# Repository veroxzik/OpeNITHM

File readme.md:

# OpeNITHM

This repository contails files related to OpeNITHM.

Firmware, schematics, board layout, and CAD files are included in this repo. Please see the CAD directory for the original 3d printed version, or the v2-cad directory for the laser cut version. 

## List of Electronics

OpeNITHM is designed for the Teensy LC.

#### Why use Teensy and not Arduino?

The biggest reason is that Teensy has built in capacitive sensing, which is how OpeNITHM fuctions. You have to fake it on Arduino using very controlled analog reads, and it is nowhere near as sensitive. In my (VXZK's) experience, it was simply impossible to use an Arduino to do the capacitive sensing required for this project.

I chose the Teensy LC as it is the lowest cost Teensy model available with capacitive sensing. The firmware and PCB are designed for this board alone; significant modifications may be required for any other version.

There is an alternative build using an Arduino Pro Micro and 2 MPR121s as a branch in this repo, but it is not maintained and not recommended. You're on your own with that one!

### Teensy LC Build

Links are mostly suggestions (except the Teensy, which is only officially available through the PJRC site and authorized resellers).  
(VXZK: I've heard a lot of trouble regarding good quality IR leds and phototransistors, so I've included specific links to the ones I purchased and has worked well for me.)  

The links below also assume you want to socket your Teensy and multiplexers for later use. You can solder them directly, if you'd like.  
If you are going to solder your sensors directly to the PCB, it is not necessary buy the 0.1" Pin Header, Right Angle. Otherwise, include female 0.1" sockets for your sensors (commonly referred to as Dupont connectors).  

| Part | Link | Qty |
| --- | --- |:---:|
| Teensy LC | https://www.pjrc.com/store/teensylc.html | 1 |
| Teensy LC Breakout Board | this Github, Circuit-Teensy32 folder contains gerbers | 1 |
| 74HC4051 Multiplexer Breakout Board | [Aliexpress][1] | 4 |
| 0.1" Pin Header, 1 row, 40 pos | [Aliexpress (qty 10)][2] | 2 |
| 0.1" Pin Header, Right Angle, 2 row, 24 pos | [LCSC][3] | 2 |
| 0.1" Socket, Straight, 1 row, 14 pos | [LCSC][4] | 2 |
| 0.1" Socket, Straight, 1 row, 5 pos | [LCSC][5] | 2 |
| 0.1" Socket, Straight, 1 row, 11 pos | [LCSC][6] | 2 |
| 0.1" Socket, Straight, 1 row, 8 pos | [LCSC][7] | 2 |
| 51k ohm Resistor, 1/6W or 1/8W | LCSC or Aliexpress | 6 |
| 33 ohm Resistor, 1/4W, 1/6W, or 1/8W | LCSC or Aliexpress | 3 |
| 1m WS2812B RGB 5V LED Strip, 30LED Per Meter | [Aliexpress][8] | 1 |
| IR LED and Phototransistor | [Ebay (Qty 20 pairs)][9] | 6 |

[1]: https://www.aliexpress.com/item/32807771098.html
[2]: https://www.aliexpress.com/item/665534073.html
[3]: https://lcsc.com/product-detail/New-Arrivals_XFCN-PZ254R-12-24P_C492440.html
[4]: https://lcsc.com/product-detail/Pin-Header-Female-Header_Boom-Precision-Elec-Female-header-2-54-1-14P_C52711.html
[5]: https://lcsc.com/product-detail/Pin-Header-Female-Header_Boom-Precision-Elec-2-54mm-1-5p-Female-header_C50950.html
[6]: https://lcsc.com/product-detail/Pin-Header-Female-Header_Changjiang-Connectors-A2541HWV-11P_C225508.html
[7]: https://lcsc.com/product-detail/Pin-Header-Female-Header_Boom-Precision-Elec-2-54mm-1-8P-Straight-Female-header_C27438.html
[8]: https://www.aliexpress.com/item/2036819167.html
[9]: https://www.ebay.com/itm/40pcs-5mm-Infrared-LED-940nm-Emitter-Diode-and-IR-Receiver-Set/252235145540

## Board Revision and Sensors

As of 2020-07-17, the recommended board version is v2.1, which features inputs for 32 sensors. This best replicates the feeling of the arcade. Previous versions used 16 sensors. If you still wish to make a 16 key version, you can order the v2.1 but only populate two of the multiplexers. This is not really recommended.

### Older versions

For v2.0 and v1.1, bridge pins 17 and 24 for best throughput of RGB lighting and select the appropriate setting in `Config.h`.

## Installing on Teensy LC

**NOTE:** This firmware is *only* written to work for the Teensy LC. Do *not* use Teensy 2.0, Teensy 3.x, or Teensy 4.x

Locate your `arduino` folder (usually `C:\Program Files (x86)\arduino`).

#### I have a fresh install of Teensyduino, or have never modified my USB profiles

Copy `Firmware/Teensy/boards.txt` to `arduino\hardware\teensy\avr\` and overwrite the existing.

Copy `Firmware/Teensy/teensy3` to `arduino\hardware\teensy\avr\cores\teensy3` and overwrite any conflicts.

Copy `Firmware/FastLED/WS2812Serial.cpp` and `Firmware/FastLED/WS2812Serial.h` to `arduino\hardware\teensy\avr\libraries\WS2812Serial` and overwrite the existing.

Copy `Firmware/FastLED/FastLED.cpp` and `Firmware/FastLED/FastLED.h` to `[My Documents]\Arduino\libraries\FastLED\` and overwrite the existing.

#### I am applying the changes manually

See [the firmware readme](Firmware/README.md) for more information.

## Configuring the Firmware and IDE

There are a number of options built into the firmware to give you flexibility in your implementation. These are presented as preprocessor defines that can be commented and uncommented to fit.

All user-editable defines are in `Config.h`, see the comments for additional information.

`PinConfig.h` contains the defintions of each pin. This does not need to be edited if using the gerbers from this repo.

If you do not have the FastLED library installed, do so though the `Tools->Manage Libraries` menu. You will also need the WS2812Serial library, which should be installed when you install Teensyduino.

#### Compiling

Select `Teensy LC` from `Tools->Board`, then select `Serial + NKRO Keyboard`.

Prior to compilation, review the (numerous) options available to the end user in `Config.h`. Comment and uncomment the corresponding options that match your setup.

## Running the Software

#### Configuring

To be revised.

#### Power On

To be revised.

#### Output

By default, the program will run in NKRO Keyboard mode. The specific keyboard keys are set in `USBOutput.cpp`, but are listed here in order of left to right:
```
a z s x d c f v g b h n j m k ,
```
When a second finger touches the pad, the following keys are pressed in order of left to right
```
1 q 2 w 3 e 4 r 5 t 6 y 7 u 8 i
```

By default, the air sensor functions as follows:
- `Home` is held as long as any sensor is triggered and released when there are no sensors triggered.
- `End` is pressed when any motion is detected, as long as the hand was previously in front of the sensors.
- `Page Up` is pressed and released when the sensor detections movement upwards.
- `Page Down` is pressed and released when the sensor detections movement downwards.

If `#define IR_SENSOR_KEY` is uncommented, each air sensor will report back individually. The default binding from bottom to top is:
```
/ . ' ; ] [
```
Per US QWERTY layout.

## Credits

Thanks to SpaghettiSnail for the LED Support Peg model!

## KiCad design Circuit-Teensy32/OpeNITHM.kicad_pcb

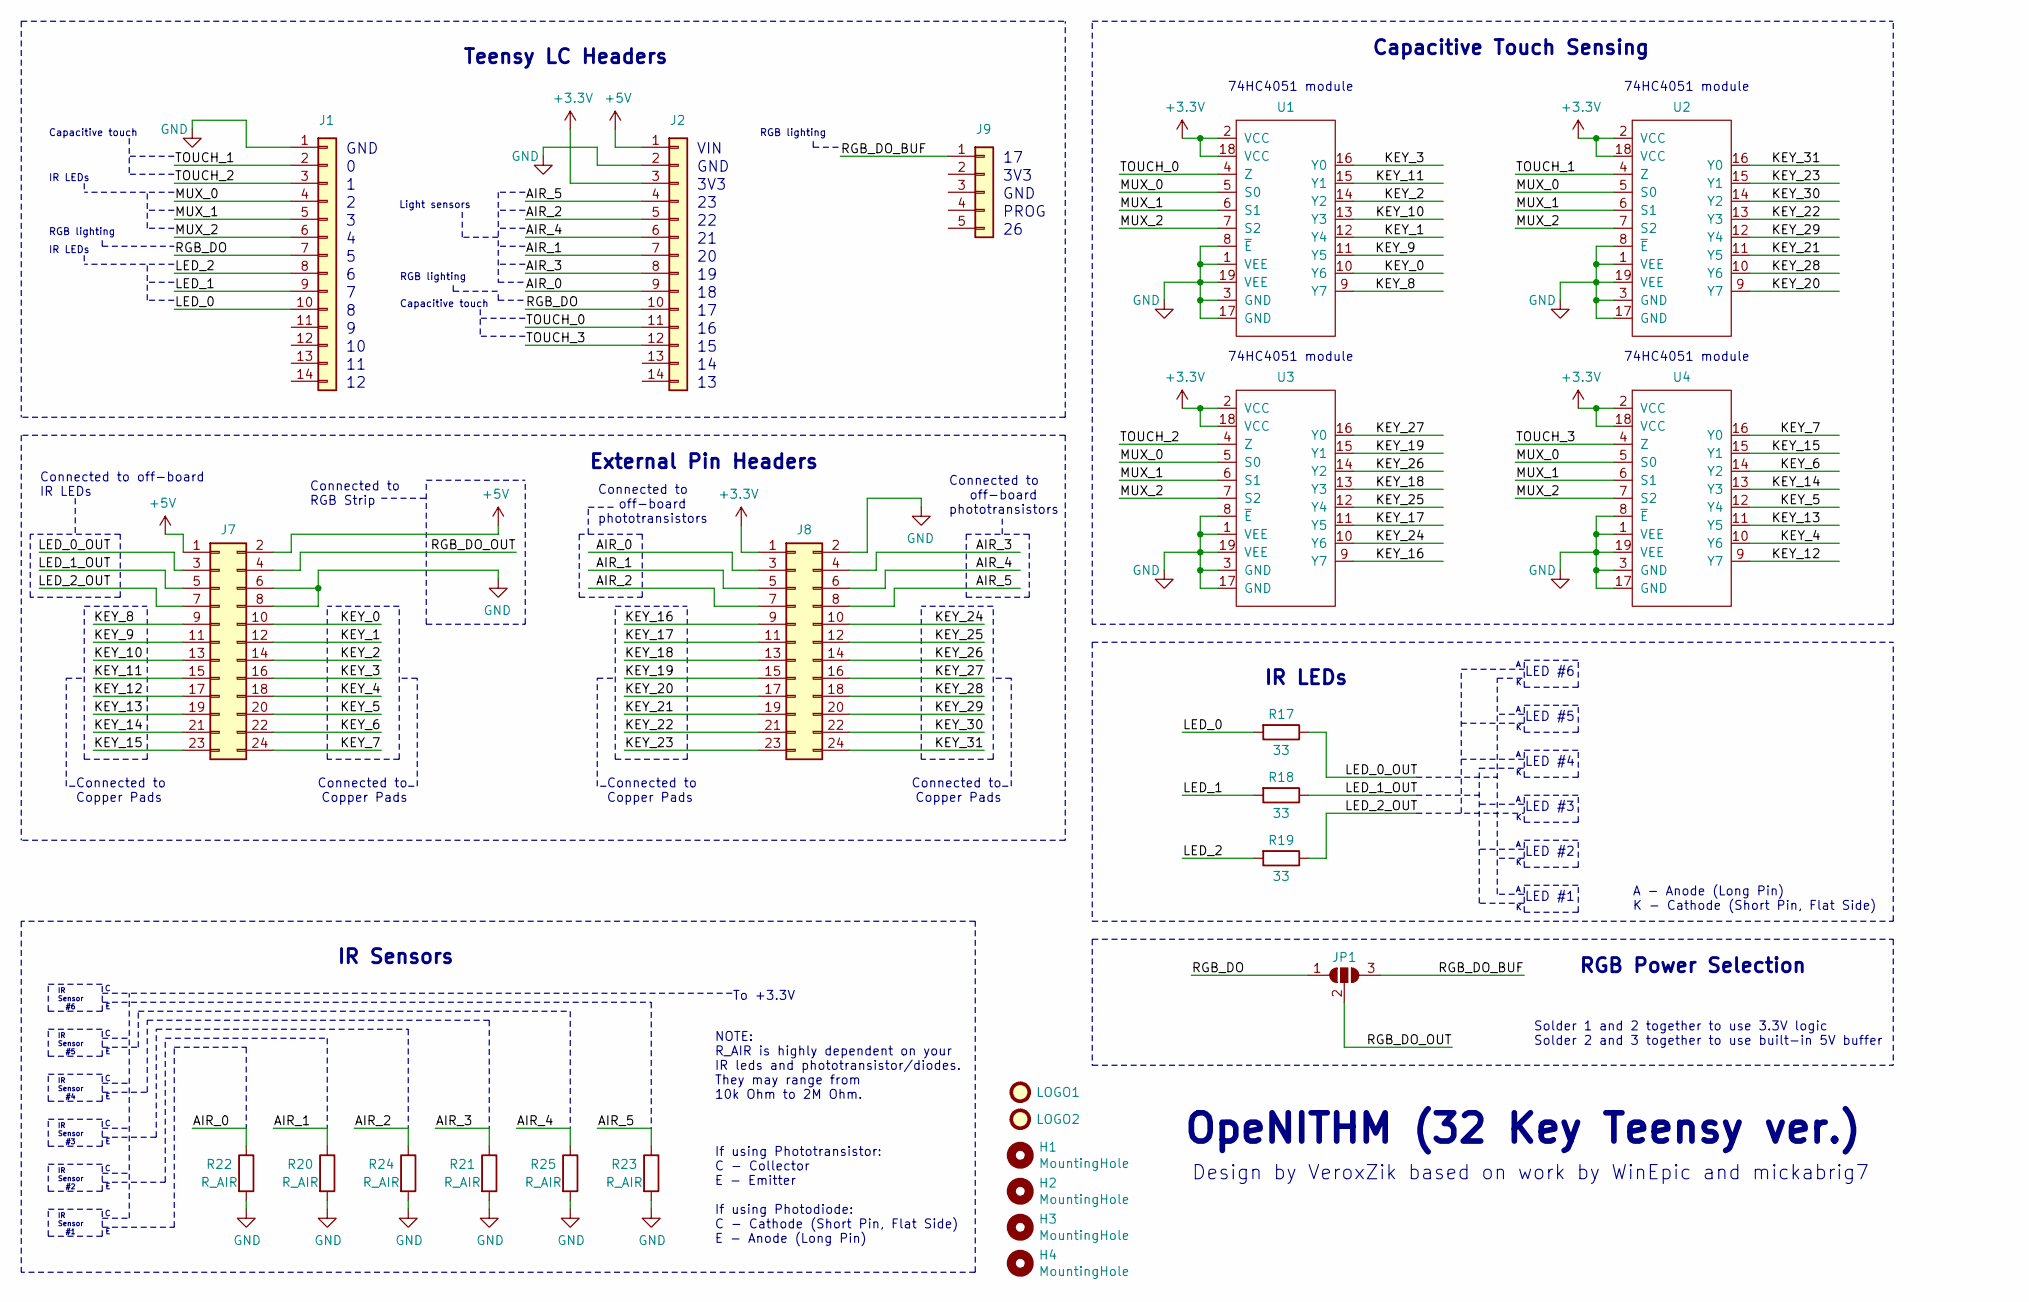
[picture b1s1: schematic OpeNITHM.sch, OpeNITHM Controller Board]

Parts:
H1, H2, H3, H4: MountingHole; MountingHole_3.2mm_M3_ISO14580
J1, J2: Conn_01x14; PinSocket_1x14_P2.54mm_Vertical
J7, J8: Conn_02x12_Odd_Even; PinHeader_2x12_P2.54mm_Horizontal
J9: Conn_01x05; PinSocket_1x05_P2.54mm_Vertical
JP1: SolderJumper_3_Open; SolderJumper-3_P1.3mm_Open_RoundedPad1.0x1.5mm
LOGO1, LOGO2: Logo; openithm-logo
R17, R18, R19: 33; R_Axial_DIN0207_L6.3mm_D2.5mm_P7.62mm_Horizontal
R20, R21, R22, R23, R24, R25: R_AIR; R_Axial_DIN0204_L3.6mm_D1.6mm_P5.08mm_Horizontal
U1, U2, U3, U4: 74HC4051; 74HC4051_Sparkfun_Aliexpress

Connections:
+3V3: J2.3, J8.1, U1.2 (VCC), U1.18 (VCC), U2.2 (VCC), U2.18 (VCC), U3.2 (VCC), U3.18 (VCC), U4.2 (VCC), U4.18 (VCC)
+5V: J2.1, J7.1, J7.2
/AIR_0: J2.9, J8.3, R22.1
/AIR_1: J2.7, J8.5, R20.1
/AIR_2: J2.5, J8.7, R24.1
/AIR_3: J2.8, J8.4, R21.1
/AIR_4: J2.6, J8.6, R25.1
/AIR_5: J2.4, J8.8, R23.1
/KEY_0: J7.10, U1.10 (Y6)
/KEY_1: J7.12, U1.12 (Y4)
/KEY_2: J7.14, U1.14 (Y2)
/KEY_3: J7.16, U1.16 (Y0)
/KEY_4: J7.18, U4.10 (Y6)
/KEY_5: J7.20, U4.12 (Y4)
/KEY_6: J7.22, U4.14 (Y2)
/KEY_7: J7.24, U4.16 (Y0)
/KEY_8: J7.9, U1.9 (Y7)
/KEY_9: J7.11, U1.11 (Y5)
/KEY_10: J7.13, U1.13 (Y3)
/KEY_11: J7.15, U1.15 (Y1)
/KEY_12: J7.17, U4.9 (Y7)
/KEY_13: J7.19, U4.11 (Y5)
/KEY_14: J7.21, U4.13 (Y3)
/KEY_15: J7.23, U4.15 (Y1)
/KEY_16: J8.9, U3.9 (Y7)
/KEY_17: J8.11, U3.11 (Y5)
/KEY_18: J8.13, U3.13 (Y3)
/KEY_19: J8.15, U3.15 (Y1)
/KEY_20: J8.17, U2.9 (Y7)
/KEY_21: J8.19, U2.11 (Y5)
/KEY_22: J8.21, U2.13 (Y3)
/KEY_23: J8.23, U2.15 (Y1)
/KEY_24: J8.10, U3.10 (Y6)
/KEY_25: J8.12, U3.12 (Y4)
/KEY_26: J8.14, U3.14 (Y2)
/KEY_27: J8.16, U3.16 (Y0)
/KEY_28: J8.18, U2.10 (Y6)
/KEY_29: J8.20, U2.12 (Y4)
/KEY_30: J8.22, U2.14 (Y2)
/KEY_31: J8.24, U2.16 (Y0)
/LED_0: J1.10, R17.2
/LED_0_OUT: J7.3, R17.1
/LED_1: J1.9, R18.2
/LED_1_OUT: J7.5, R18.1
/LED_2: J1.8, R19.2
/LED_2_OUT: J7.7, R19.1
/MUX_0: J1.4, U1.5 (S0), U2.5 (S0), U3.5 (S0), U4.5 (S0)
/MUX_1: J1.5, U1.6 (S1), U2.6 (S1), U3.6 (S1), U4.6 (S1)
/MUX_2: J1.6, U1.7 (S2), U2.7 (S2), U3.7 (S2), U4.7 (S2)
/RGB_DO: J1.7, J2.10, JP1.1 (A)
/RGB_DO_BUF: J9.1, JP1.3 (B)
/RGB_DO_OUT: J7.4, JP1.2 (C)
/TOUCH_0: J2.11, U1.4 (Z)
/TOUCH_1: J1.2, U2.4 (Z)
/TOUCH_2: J1.3, U3.4 (Z)
/TOUCH_3: J2.12, U4.4 (Z)
GND: J1.1, J2.2, J7.6, J7.8, J8.2, R20.2, R21.2, R22.2, R23.2, R24.2, R25.2, U1.1 (VEE), U1.3 (GND), U1.8 (~E), U1.17 (GND), U1.19 (VEE), U2.1 (VEE), U2.3 (GND), U2.8 (~E), U2.17 (GND), U2.19 (VEE), U3.1 (VEE), U3.3 (GND), U3.8 (~E), U3.17 (GND), U3.19 (VEE), U4.1 (VEE), U4.3 (GND), U4.8 (~E), U4.17 (GND), U4.19 (VEE)

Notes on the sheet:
Capacitive Touch Sensing
Teensy LC Headers
RGB lighting
OpeNITHM (32 Key Teensy ver.)
Design by VeroxZik based on work by WinEpic and mickabrig7
Connected to off-board phototransistors
IR Sensors
IR LEDs
LED #1
74HC4051 module
LED #2
LED #3
LED #4
LED #5
LED #6
IR Sensor #6
GND
VIN
3V3
Capacitive touch
PROG
External Pin Headers
Connected to off-board IR LEDs
RGB Power Selection
Connected to RGB Strip
A - Anode (Long Pin) K - Cathode (Short Pin, Flat Side)
Solder 1 and 2 together to use 3.3V logic Solder 2 and 3 together to use built-in 5V buffer
To +3.3V
If using Phototransistor: C - Collector E - Emitter If using Photodiode: C - Cathode (Short Pin, Flat Side) E - Anode (Long Pin)
IR Sensor #5
IR Sensor #4
IR Sensor #3
IR Sensor #2
IR Sensor #1
Light sensors
Connected to Copper Pads
NOTE: R_AIR is highly dependent on your IR leds and phototransistor/diodes. They may range from 10k Ohm to 2M Ohm.

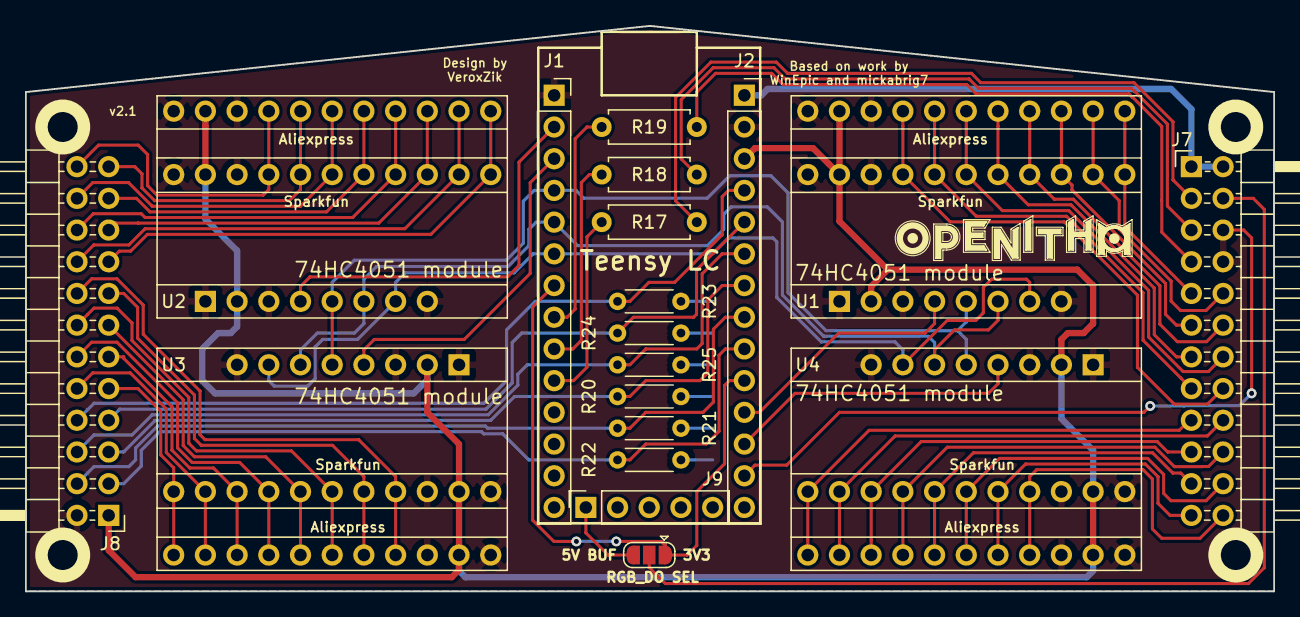
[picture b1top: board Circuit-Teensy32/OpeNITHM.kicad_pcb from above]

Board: 2 copper layers, 100.0 x 45.3 mm, 25 parts (1 on the bottom side), 57 nets.

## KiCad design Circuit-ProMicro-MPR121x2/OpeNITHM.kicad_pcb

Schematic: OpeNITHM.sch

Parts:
C1, C2: 35V 10uF; CP_Radial_D5.0mm_P2.00mm
J1, J2, J4, J6: Conn_01x12; PinSocket_1x12_P2.54mm_Vertical
J3, J5, J9, J10: Conn_01x06; PinSocket_1x06_P2.54mm_Vertical
J7, J8: Conn_02x08_Odd_Even; PinHeader_2x08_P2.54mm_Horizontal
JP1, JP3, JP4: SolderJumper_2_Open; SolderJumper-2_P1.3mm_Open_RoundedPad1.0x1.5mm
JP2: SolderJumper_2_Bridged; SolderJumper-2_P1.3mm_Bridged_RoundedPad1.0x1.5mm
MH1, MH2, MH3, MH4: MountingHole; MountingHole_3.2mm_M3_ISO7380
R1, R2, R3: 33; R_Axial_DIN0204_L3.6mm_D1.6mm_P5.08mm_Horizontal
R4, R5, R6, R7, R8, R9: 51k; R_Axial_DIN0204_L3.6mm_D1.6mm_P5.08mm_Horizontal
U1: L4931CZ33; TO-92_Inline_Wide

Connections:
+3V3: C2.1, J3.1, J5.1, J8.2, J10.4, JP1.2, JP2.1, U1.1 (VO)
+5V: C1.1, J2.1, J7.10, J9.4, U1.3 (VI)
/AIR_0: J2.8, J8.4, R4.1
/AIR_1: J2.12, J8.6, R5.1
/AIR_2: J1.12, J8.8, R6.1
/AIR_3: J2.5, J8.10, R7.1
/AIR_4: J2.6, J8.12, R8.1
/AIR_5: J2.7, J8.14, R9.1
/KEY_0: J4.8, J7.1
/KEY_1: J4.7, J7.3
/KEY_2: J4.6, J7.5
/KEY_3: J4.5, J7.7
/KEY_4: J4.4, J7.9
/KEY_5: J4.3, J7.11
/KEY_6: J4.2, J7.13
/KEY_7: J4.1, J7.15
/KEY_8: J6.12, J8.1
/KEY_9: J6.11, J8.3
/KEY_10: J6.10, J8.5
/KEY_11: J6.9, J8.7
/KEY_12: J6.8, J8.9
/KEY_13: J6.7, J8.11
/KEY_14: J6.6, J8.13
/KEY_15: J6.5, J8.15
/LED_0: J1.11, R1.2
/LED_0_OUT: J7.2, R1.1
/LED_1: J1.10, R2.2
/LED_1_OUT: J7.4, R2.1
/LED_2: J1.9, R3.2
/LED_2_OUT: J7.6, R3.1
/RGB_CO: J2.9, J7.14
/RGB_DO: J2.11, J7.12
/SCL_H: J1.6, J9.5, JP3.1
/SCL_L: J3.3, J5.3, J10.5, JP3.2
/SDA_H: J1.5, J9.6, JP4.1
/SDA_L: J3.4, J5.4, J10.6, JP4.2
GND: C1.2, C2.2, J1.3, J1.4, J2.2, J3.6, J5.6, J7.16, J8.16, J9.3, J10.3, R4.2, R5.2, R6.2, R7.2, R8.2, R9.2, U1.2 (GND)
unnamed: J5.5, JP2.2
VCC: J2.4, JP1.1

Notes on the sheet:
Capacitive Touch Sensing
Pro Micro Headers
2019/06/27
OpeNITHM controller board
OpeNITHM (MPR121 Variant)
Design by VeroxZik
Connected to off-board phototransistors
IR Sensors
IR LEDs
LED #1
LED #2
LED #3
LED #4
LED #5
LED #6
IR Sensor #6
External Pin Headers
Connected to off-board Charlieplexed LEDs
Level Shifter
Connected to Copper Pads
Connected to RGB Strip
A - Anode (Long Pin) K - Cathode (Short Pin, Flat Side)
To +3.3V
If using Phototransistor: C - Collector E - Emitter If using Photodiode: C - Cathode (Short Pin, Flat Side) E - Anode (Long Pin)
IR Sensor #5
IR Sensor #4
IR Sensor #3
IR Sensor #2
IR Sensor #1
GND
D9/A9
RST
VCC
RAW
D20/A2
D21/A3
D18/A0
D19/A1
D14/MISO
D15/SCLK

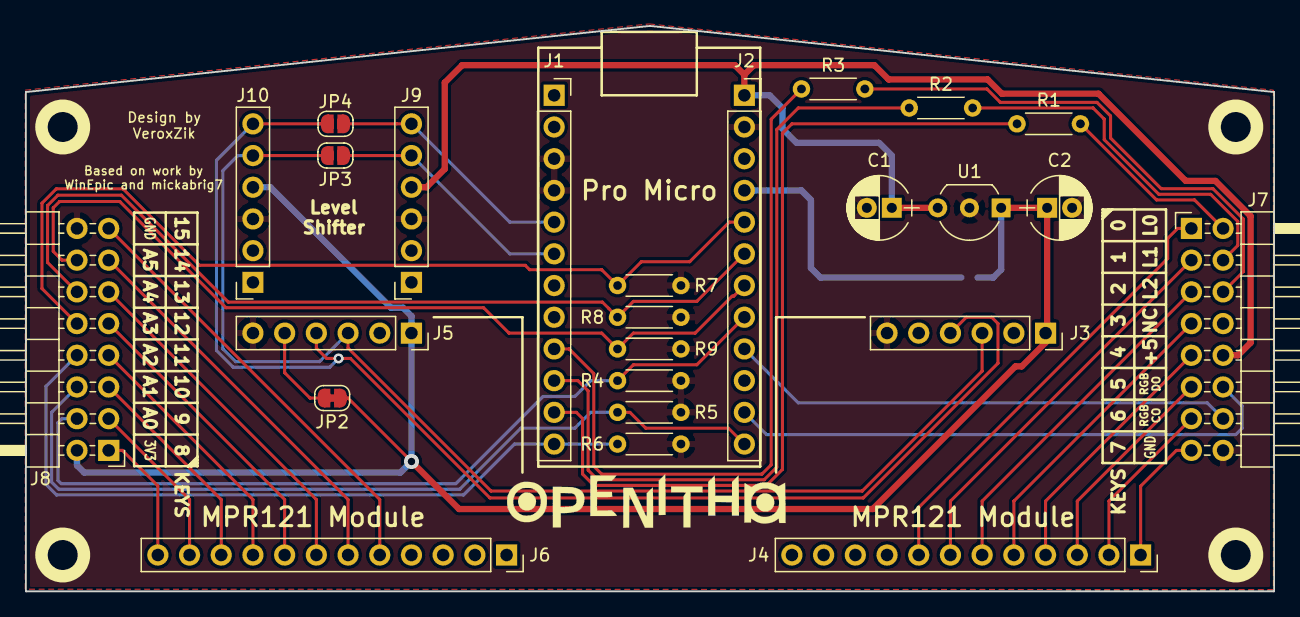
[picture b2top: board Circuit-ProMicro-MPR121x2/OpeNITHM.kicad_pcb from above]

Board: 2 copper layers, 100.0 x 45.3 mm, 30 parts (1 on the bottom side), 39 nets.

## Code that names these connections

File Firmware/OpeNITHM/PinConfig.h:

#include "Config.h"

#ifndef _PINCONFIG_h
#define _PINCONFIG_h

// Multiplexer pin settings
#if defined(OPENITHM_V1_0)
#define MUX_0 20
#define MUX_1 19
#define MUX_2 18
#elif defined(OPENITHM_V1_1)
#define MUX_0 2
#define MUX_1 1
#define MUX_2 0
#elif defined(OPENITHM_V2_0)
#define MUX_0 0
#define MUX_1 1
#define MUX_2 2
#elif defined(OPENITHM_V2_1)
#define MUX_0 2
#define MUX_1 3
#define MUX_2 4
#elif defined(OPENITHM_FULL_V1_0)
#define MUX_0 4
#define MUX_1 3
#define MUX_2 2
#endif

// Sensor pin settings
#if defined(OPENITHM_V1_0)
#define LED_0 16
#define LED_1 21
#define LED_2 5
#elif defined(OPENITHM_V1_1) || defined(OPENITHM_V2_0)
#define LED_0 7
#define LED_1 6
#define LED_2 5
#elif defined(OPENITHM_V2_1) || defined(OPENITHM_FULL_V1_0)
#define LED_0 8
#define LED_1 7
#define LED_2 6
#endif

#ifdef IR_SENSOR_MULTIPLEXED
#define SENSOR_IN A0
#else
#if defined(OPENITHM_V1_0)
#define AIR_SENSOR_0_PIN 10
#define AIR_SENSOR_1_PIN 11
#define AIR_SENSOR_2_PIN 12
#define AIR_SENSOR_3_PIN 6
#define AIR_SENSOR_4_PIN 8
#define AIR_SENSOR_5_PIN 9
#elif defined(OPENITHM_V1_1)
#define AIR_SENSOR_0_PIN 20
#define AIR_SENSOR_1_PIN 19
#define AIR_SENSOR_2_PIN 18
#define AIR_SENSOR_3_PIN 23
#define AIR_SENSOR_4_PIN 22
#define AIR_SENSOR_5_PIN 21
#elif defined(OPENITHM_V2_0) || defined(OPENITHM_V2_1) || defined(OPENITHM_FULL_V1_0)
#define AIR_SENSOR_0_PIN 18
#define AIR_SENSOR_1_PIN 20
#define AIR_SENSOR_2_PIN 22
#define AIR_SENSOR_3_PIN 19
#define AIR_SENSOR_4_PIN 21
#define AIR_SENSOR_5_PIN 23
#endif
#endif

// Capsense pin settings
#if defined(OPENITHM_V1_0)
#define TOUCH_0 22
#define TOUCH_1 23
#elif defined(OPENITHM_V1_1)
#define TOUCH_0 16
#define TOUCH_1 3
#elif defined(OPENITHM_V2_0)
#define TOUCH_0 16
#define TOUCH_1 3
#define TOUCH_2 4
#define TOUCH_3 15
#elif defined(OPENITHM_V2_1)
#define TOUCH_0 16
#define TOUCH_1 0
#define TOUCH_2 1
#define TOUCH_3 15
#elif defined(OPENITHM_FULL_V1_0)
#define TOUCH_0 1
#define TOUCH_1 15
#define TOUCH_2 16
#define TOUCH_3 0
#endif

// Lighting pin settings
#ifdef USE_DMA_RGB
  #define LED_TYPE    WS2812SERIAL
  #define LED_ORDER   BRG
#else
  #define LED_TYPE    WS2812B
  #define LED_ORDER   GRB
#endif

#if defined(OPENITHM_V1_0)
  #define RGBPIN 4
#elif defined(OPENITHM_V1_1) || defined(OPENITHM_V2_0)
    #ifdef USE_DMA_RGB
       #define RGBPIN 24
    #else
       #define RGBPIN 11
    #endif
#elif defined(OPENITHM_V2_1) || defined(OPENITHM_FULL_V1_0)
  #define RGBPIN 5
#endif

#endif  // _PINCONFIG_h

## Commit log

2020-01-05 Initial Commit for Pro Micro + MPR121 Branch
    Must uncomment #defien USE_MPR121 first
2020-01-12 Added PDF
2020-05-19 Updated ebay link for IR leds and phototransistor
2020-05-23 Fixed typo in PinConfig.h
2020-05-26 Added AirSensorTest.ino
2020-06-04 Initial Commit of 32 key Teensy variant
2020-06-06 Fix Teensy v1.0 define typo
2020-06-07 Initial 32 key commit
    Added 32 keys per 2.0 schematic
    Changed touch sensing to enums vs. bool and propagated changes
2020-06-09 Updated CAD files
2020-06-09 Updated readme with wiki link
2020-06-09 Removed LED Clamp from CAD and moved old files to CAD/Obsolete
2020-06-11 Updated Readme, added LED Support peg model
2020-06-14 Fixed no outputs in 32 key mode
2020-06-28 Create LED retaining Peg v1.f3d
    Adding source files for LED retaining peg, which was added a little bit ago.
2020-07-07 Updated LED Retaining Peg, Added STEP Files
2020-07-09 Update 32 key board to v2.1
    Reorganizes pins so DMA can be used, drops APA102 support, adds additional pins for complex IR LED boards.
2020-07-10 Added revision disclaimer
2020-07-18 Changes to v2.1
    Broke out all spare pins to Teensy,
    No more solder jumper for RGB data line,
    Added solder jumper for IR LED power option (+5v by default)
2020-07-18 Moves 16 key board to "Depreciated" folder
    (Just use the 32 key one)
2020-07-18 Updates README for 32 key
2020-07-18 Updated firmware for v2.1, removed Pro Micro support
2020-08-10 Update 3D Printed CAD readme
2020-11-22 Fix -1 array bug
    Key 30 was being pressed every loop, making it stuck. The key divider code was accessing a negative array, overwriting other variables, causing this.
2020-11-27 Fixed RGB labeling on back silkscreen
2020-12-08 Restore / reorganize 3D printed CAD
    Added Single Layer and Dual Layer into separate folders in STL.
2020-12-13 Fixed Serial Plot, added more debug defines
2020-12-15 Add preliminary full PCB support based on the current prototype, and fix some air tower issues
